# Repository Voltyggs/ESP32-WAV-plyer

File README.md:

# ESP32-WAV-plyer
A lil 8bit 44.1KHz mono .WAv player i built with the ESP32

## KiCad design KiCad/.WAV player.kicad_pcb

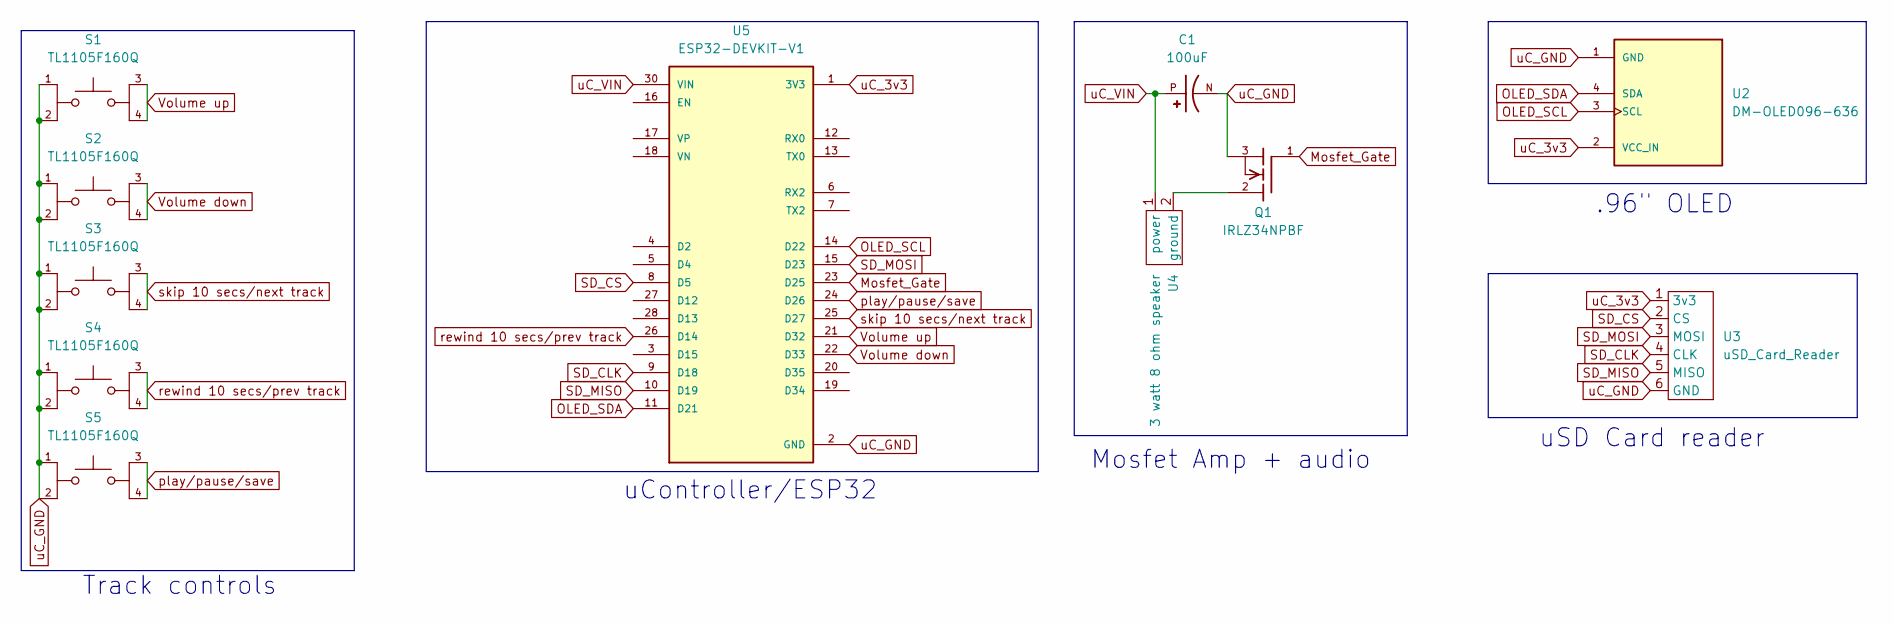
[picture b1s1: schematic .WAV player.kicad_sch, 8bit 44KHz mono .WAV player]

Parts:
C1: 100uF; CAPPRD250W50D500H1100; PARTREV 20-DEC-19
Q1: IRLZ34NPBF; IRLZ34NPBF_ENG
S1, S2, S3, S4, S5: TL1105F160Q; SW_TL1105F160Q; PARTREV A
U2: DM-OLED096-636; MODULE_DM-OLED096-636; PARTREV 2018-09-10
U3: uSD_Card_Reader; 1_micro_SD_card_reader
U4: 3 watt 8 ohm speaker; 2_3W_8O_Speaker
U5: ESP32-DEVKIT-V1; MODULE_ESP32_DEVKIT_V1; PARTREV N/A

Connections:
Mosfet_Gate: Q1.1, U5.23 (D25); also elsewhere on the board
unnamed: Q1.2, U4.2 (ground)
OLED_SCL: U2.3 (SCL), U5.14 (D22); also elsewhere on the board
OLED_SDA: U2.4 (SDA), U5.11 (D21); also elsewhere on the board
SD_CLK: U3.4 (CLK), U5.9 (D18); also elsewhere on the board
SD_CS: U3.2 (CS), U5.8 (D5); also elsewhere on the board
SD_MISO: U3.5 (MISO), U5.10 (D19); also elsewhere on the board
SD_MOSI: U3.3 (MOSI), U5.15 (D23); also elsewhere on the board
Volume down: S2.3, S2.4, U5.22 (D33); also elsewhere on the board
Volume up: S1.3, S1.4, U5.21 (D32); also elsewhere on the board
play/pause/save: S5.3, S5.4, U5.24 (D26); also elsewhere on the board
rewind 10 secs/prev track: S4.3, S4.4, U5.26 (D14); also elsewhere on the board
skip 10 secs/next track: S3.3, S3.4, U5.25 (D27); also elsewhere on the board
uC_3v3: U2.2 (VCC_IN), U3.1 (3v3), U5.1 (3V3); also elsewhere on the board
uC_GND: C1.N, Q1.3, S1.1, S1.2, S2.1, S2.2, S3.1, S3.2, S4.1, S4.2, S5.1, S5.2, U2.1 (GND), U3.6 (GND), U5.2 (GND), U5.29 (GND); also elsewhere on the board
uC_VIN: C1.P, U4.1 (power), U5.30 (VIN); also elsewhere on the board

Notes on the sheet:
uSD Card reader
Mosfet Amp + audio
.96" OLED
Track controls
uController/ESP32

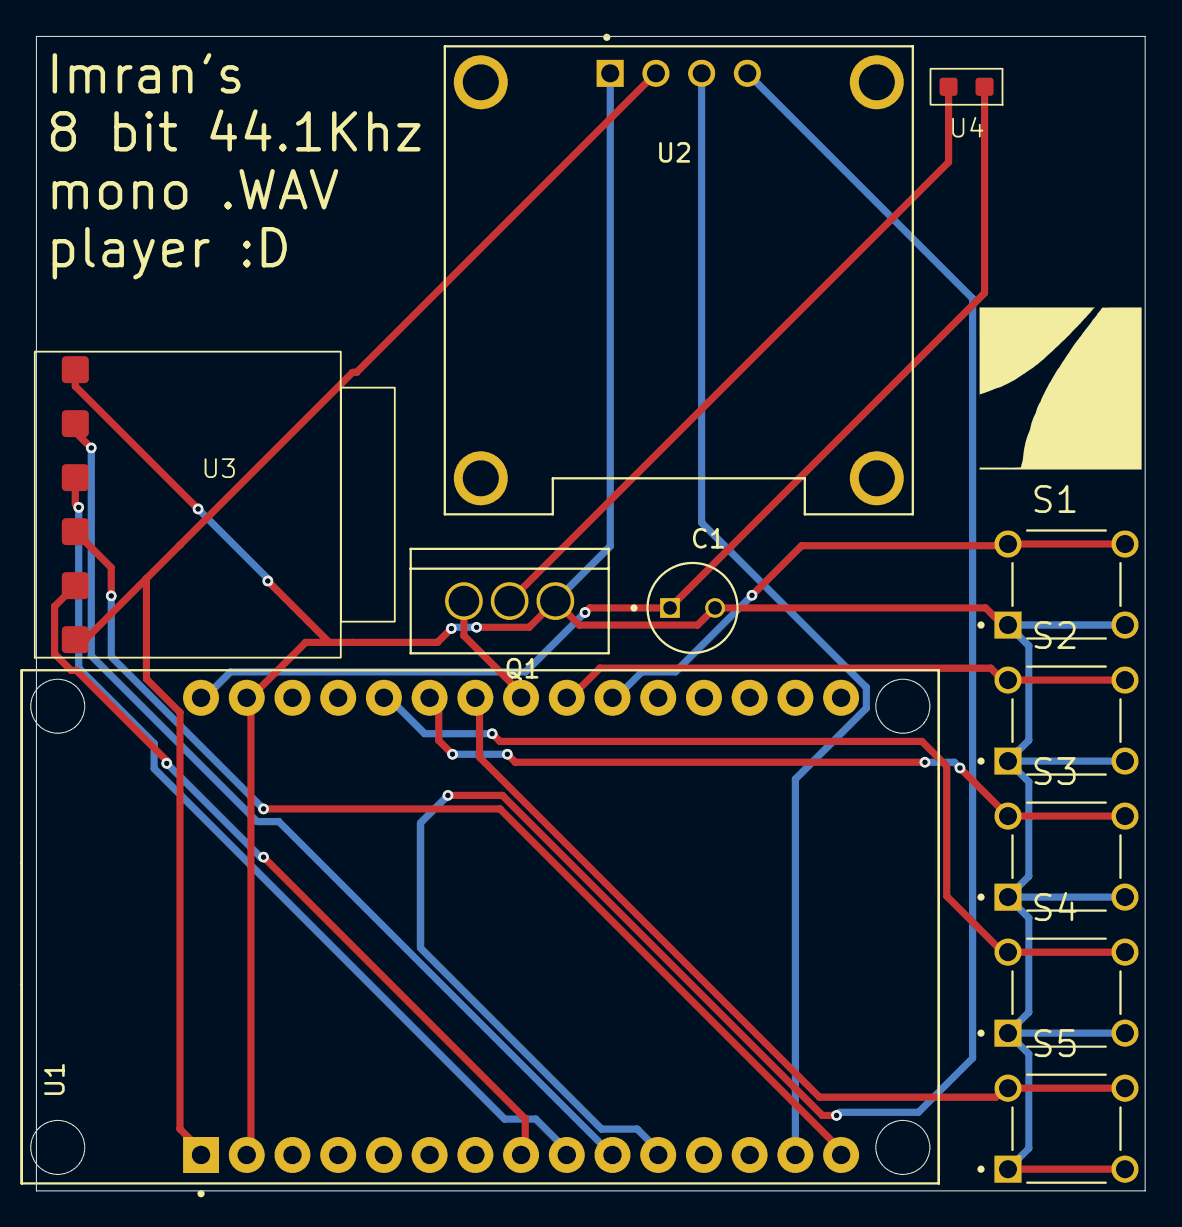
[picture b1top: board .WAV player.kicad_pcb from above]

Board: 2 copper layers, 61.6 x 64.1 mm, 11 parts (0 on the bottom side), 16 nets.

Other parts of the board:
U1: ESP32-DEVKIT-V1; MODULE_ESP32_DEVKIT_V1

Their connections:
Mosfet_Gate: U1.23 (D25); also elsewhere on the board
OLED_SCL: U1.14 (D22); also elsewhere on the board
OLED_SDA: U1.11 (D21); also elsewhere on the board
SD_CLK: U1.9 (D18); also elsewhere on the board
SD_CS: U1.8 (D5); also elsewhere on the board
SD_MISO: U1.10 (D19); also elsewhere on the board
SD_MOSI: U1.15 (D23); also elsewhere on the board
Volume down: U1.22 (D33); also elsewhere on the board
Volume up: U1.21 (D32); also elsewhere on the board
play/pause/save: U1.24 (D26); also elsewhere on the board
rewind 10 secs/prev track: U1.26 (D14); also elsewhere on the board
skip 10 secs/next track: U1.25 (D27); also elsewhere on the board
uC_3v3: U1.1 (3V3); also elsewhere on the board
uC_GND: U1.2 (GND), U1.29 (GND); also elsewhere on the board
uC_VIN: U1.30 (VIN); also elsewhere on the board

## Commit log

2025-12-11 Create temp
2025-12-11 Add installation note for Adafruit SSD1306 library
